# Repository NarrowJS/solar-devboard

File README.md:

## Solar Devboard
An ESP32 C6 mini based devboard that combines zigbee/wifi with solar and lipo charging to easily deploy remote sensing IOT devices.

## Features
- 3.7v Lipo charging circuit and JST connector
- Support for 3v - 18v solar panels
- Reverse polarity protection on solar panel connector
- ADC for lipo charge monitoring
- Power path for charging while on usb-c power
- Extremely compact form factor
- M2 mounting holes

## Why
- Solar panels are extremely useful for remote sensing applications to provide a power source without long wires or very large batteries
- Most solar projects require boost converters and extra breakout boards to connect lipo batteries safely
- Most solar charging boards are too large to be used in compact applications

## BOM
| Reference             | Value                       | Datasheet                                                                         | Footprint                                                  | Qty | DNP | Link                                                                                                                                                                                                                |
|-----------------------|-----------------------------|-----------------------------------------------------------------------------------|------------------------------------------------------------|-----|-----|---------------------------------------------------------------------------------------------------------------------------------------------------------------------------------------------------------------------|
| C1,C2,C4,C5,C10       | 100nF                       | ~                                                                                 | Capacitor_SMD:C_0402_1005Metric                            | 5   |     | https://www.lcsc.com/product-detail/C60474.html?s_z=n_q_100nF%25200402&spm=wm.ssy.bg.0.xh&lcsc_vid=RgcMVwVXQVAIVFxUQVdZVlNSTgBWA1RfFlNeVwIDFAcxVlNRQFRXXl1RT1heUTsOAxUeFF5JWBYZEEoKFBINSQcJGk4%3D                   |
| C3,C6,C12             | 10uF                        | ~                                                                                 | Capacitor_SMD:C_0603_1608Metric                            | 3   |     | https://www.lcsc.com/product-detail/C19702.html?s_z=n_q_10uF%25200603&spm=wm.ssy.bg.0.xh&lcsc_vid=RgcMVwVXQVAIVFxUQVdZVlNSTgBWA1RfFlNeVwIDFAcxVlNRQFdeV1RXRVhcVjsOAxUeFF5JWBYZEEoKFBINSQcJGk4dAgUUFAk%3D            |
| C7                    | 1uF                         | ~                                                                                 | Capacitor_SMD:C_0402_1005Metric                            | 1   |     | https://www.lcsc.com/product-detail/C19702.html?s_z=n_q_10uF%25200603&spm=wm.ssy.bg.0.xh&lcsc_vid=RgcMVwVXQVAIVFxUQVdZVlNSTgBWA1RfFlNeVwIDFAcxVlNRQFdeV1RXRVhcVjsOAxUeFF5JWBYZEEoKFBINSQcJGk4dAgUUFAk%3D            |
| D1                    | CHARGE LED                  | ~                                                                                 | LED_SMD:LED_0805_2012Metric                                | 1   |     | https://www.lcsc.com/product-detail/C19702.html?s_z=n_q_10uF%25200603&spm=wm.ssy.bg.0.xh&lcsc_vid=RgcMVwVXQVAIVFxUQVdZVlNSTgBWA1RfFlNeVwIDFAcxVlNRQFdeV1RXRVhcVjsOAxUeFF5JWBYZEEoKFBINSQcJGk4dAgUUFAk%3D            |
| D2,D3,D4              | 1N5819WS                    | https://datasheet.lcsc.com/lcsc/2204281430_Guangdong-Hottech-1N5819WS_C191023.pdf | Diode_SMD:D_SOD-323                                        | 3   |     | https://www.lcsc.com/product-detail/C191023.html?s_z=n_q_1N5819WS&spm=wm.ssy.bg.0.xh&lcsc_vid=RgcMVwVXQVAIVFxUQVdZVlNSTgBWA1RfFlNeVwIDFAcxVlNRQFdeV1RRQFleUzsOAxUeFF5JWBYZEEoKFBINSQcJGk4dAgUUFAk%3D                |
| IC1                   | RT9080-33GJ5                |                                                                                   | RT9080-33GJ5:SOT94P280X100-5N                              | 1   |     | https://www.lcsc.com/product-detail/C191023.html?s_z=n_q_1N5819WS&spm=wm.ssy.bg.0.xh&lcsc_vid=RgcMVwVXQVAIVFxUQVdZVlNSTgBWA1RfFlNeVwIDFAcxVlNRQFdeV1RRQFleUzsOAxUeFF5JWBYZEEoKFBINSQcJGk4dAgUUFAk%3D                |
| J1                    | USB_C_Receptacle_USB2.0_14P | https://www.usb.org/sites/default/files/documents/usb_type-c.zip                  | Connector_USB:USB_C_Receptacle_HRO_TYPE-C-31-M-12          | 1   |     | https://www.lcsc.com/product-detail/C165948.html?s_z=n_q_type%2520c&spm=wm.ssy.bg.2.xh&lcsc_vid=RgcMVwVXQVAIVFxUQVdZVlNSTgBWA1RfFlNeVwIDFAcxVlNRQFdeV1VQTlhdVzsOAxUeFF5JWBYZEEoKFBINSQcJGk4dAgUUFAk%3D              |
| J2                    | SOLAR_IN +                  | ~                                                                                 | Connector_Wire:SolderWirePad_1x01_SMD_1x2mm                | 1   |     |                                                                                                                                                                                                                     |
| J3                    | SOLAR_IN -                  | ~                                                                                 | Connector_Wire:SolderWirePad_1x01_SMD_1x2mm                | 1   |     |                                                                                                                                                                                                                     |
| J4,J5                 | Conn_01x10_Pin              | ~                                                                                 | Connector_PinHeader_2.54mm:PinHeader_1x10_P2.54mm_Vertical | 2   |     | https://www.lcsc.com/product-detail/C42431810.html?s_z=n_q_pinheader%25201x10&spm=wm.ssy.bg.7.xh&lcsc_vid=RgcMVwVXQVAIVFxUQVdZVlNSTgBWA1RfFlNeVwIDFAcxVlNRQFdeV1BeQFJXXzsOAxUeFF5JWBYZEEoKFBINSQcJGk4dAgUUFAk%3D    |
| J6                    | 4328                        |                                                                                   | 4328:ADAFRUIT_4328                                         | 1   |     | https://www.adafruit.com/product/4328                                                                                                                                                                               |
| P1                    | S2B-PH-SM4-TB               |                                                                                   | S2B-PH-SM4-TB:JST_S2B-PH-SM4-TB                            | 1   |     | https://www.lcsc.com/product-detail/C295747.html?s_z=n_q_S2B-PH-SM4-TB&spm=wm.ssy.bg.1.xh&lcsc_vid=RgcMVwVXQVAIVFxUQVdZVlNSTgBWA1RfFlNeVwIDFAcxVlNRQFdeV1ZVQ1NcVzsOAxUeFF5JWBYZEEoKFBINSQcJGk4dAgUUFAk%3D           |
| Q2                    | AO3401A                     | http://www.aosmd.com/pdfs/datasheet/AO3401A.pdf                                   | Package_TO_SOT_SMD:SOT-23                                  | 1   |     | https://www.lcsc.com/product-detail/C15127.html?s_z=n_q_AO3401A&spm=wm.ssy.bg.0.xh&lcsc_vid=RgcMVwVXQVAIVFxUQVdZVlNSTgBWA1RfFlNeVwIDFAcxVlNRQFdeV1ZTRlRcUDsOAxUeFF5JWBYZEEoKFBINSQcJGk4dAgUUFAk%3D                  |
| R1,R2                 | 5k1                         | ~                                                                                 | Resistor_SMD:R_0603_1608Metric                             | 2   |     | https://www.lcsc.com/product-detail/C15127.html?s_z=n_q_AO3401A&spm=wm.ssy.bg.0.xh&lcsc_vid=RgcMVwVXQVAIVFxUQVdZVlNSTgBWA1RfFlNeVwIDFAcxVlNRQFdeV1ZTRlRcUDsOAxUeFF5JWBYZEEoKFBINSQcJGk4dAgUUFAk%3D                  |
| R3,R4,R5,R6,R8,R9,R10 | 10k                         | ~                                                                                 | Resistor_SMD:R_0603_1608Metric                             | 7   |     | https://www.lcsc.com/product-detail/C98220.html?s_z=n_q_10k%25200603&spm=wm.ssy.bg.0.xh&lcsc_vid=RgcMVwVXQVAIVFxUQVdZVlNSTgBWA1RfFlNeVwIDFAcxVlNRQFdeV1dUQVVeVjsOAxUeFF5JWBYZEEoKFBINSQcJGk4dAgUUFAk%3D             |
| R7                    | 1k                          | ~                                                                                 | Resistor_SMD:R_0603_1608Metric                             | 1   |     | https://www.lcsc.com/product-detail/C2907002.html?s_z=n_q_1k%25200603&spm=wm.ssy.bg.1.xh&lcsc_vid=RgcMVwVXQVAIVFxUQVdZVlNSTgBWA1RfFlNeVwIDFAcxVlNRQFdeV1dVTllXVDsOAxUeFF5JWBYZEEoKFBINSQcJGk4dAgUUFAk%3D            |
| R11                   | 27k                         | ~                                                                                 | Resistor_SMD:R_0603_1608Metric                             | 1   |     | https://www.lcsc.com/product-detail/C22967.html?s_z=n_q_27k%25200603&spm=wm.ssy.bg.0.xh&lcsc_vid=RgcMVwVXQVAIVFxUQVdZVlNSTgBWA1RfFlNeVwIDFAcxVlNRQFdeV1dQRFNXUTsOAxUeFF5JWBYZEEoKFBINSQcJGk4dAgUUFAk%3D             |
| R12,R15               | 100k                        | ~                                                                                 | Resistor_SMD:R_0603_1608Metric                             | 2   |     | https://www.lcsc.com/product-detail/C14675.html?s_z=n_q_100k%25200603&spm=wm.ssy.bg.0.xh&lcsc_vid=RgcMVwVXQVAIVFxUQVdZVlNSTgBWA1RfFlNeVwIDFAcxVlNRQFdeV1BWQVdeUTsOAxUeFF5JWBYZEEoKFBINSQcJGk4dAgUUFAk%3D            |
| SW1,SW2               | PTS810_SJM_250_SMTR_LFS     |                                                                                   | PTS810_SJM_250_SMTR_LFS:SW_PTS810_SJM_250_SMTR_LFS         | 2   |     | https://www.lcsc.com/product-detail/C116501.html?s_z=n_q_PTS810_SJM_250_SMTR_LFS&spm=wm.ssy.bg.0.xh&lcsc_vid=RgcMVwVXQVAIVFxUQVdZVlNSTgBWA1RfFlNeVwIDFAcxVlNRQFdeV1dfR1ldUDsOAxUeFF5JWBYZEEoKFBINSQcJGk4dAgUUFAk%3D |
| U1                    | ESP32-C6-MINI-1-H4          |                                                                                   | ESP32-C6-MINI-1-H4:XCVR_ESP32-C6-MINI-1-H4                 | 1   |     | https://www.lcsc.com/product-detail/C5736265.html?s_z=n_q_esp32&spm=wm.ssy.bg.25.xh&lcsc_vid=RgcMVwVXQVAIVFxUQVdZVlNSTgBWA1RfFlNeVwIDFAcxVlNRQFdeV1BUQFhZUzsOAxUeFF5JWBYZEEoKFBINSQcJGk4dAgUUFAk%3D                 |
| U2                    | PQ25186DLHR                 | https://www.ti.com/lit/gpn/bq25186                                                | BQ25186:WSON10_DLH_TEX                                     | 1   |     | https://www.lcsc.com/product-detail/C44639442.html?s_z=n_q_PQ25186DLHR&spm=wm.ssy.bg.0.xh&lcsc_vid=RgcMVwVXQVAIVFxUQVdZVlNSTgBWA1RfFlNeVwIDFAcxVlNRQFdeV1BQRFdZVDsOAxUeFF5JWBYZEEoKFBINSQcJGk4dAgUUFAk%3D           |

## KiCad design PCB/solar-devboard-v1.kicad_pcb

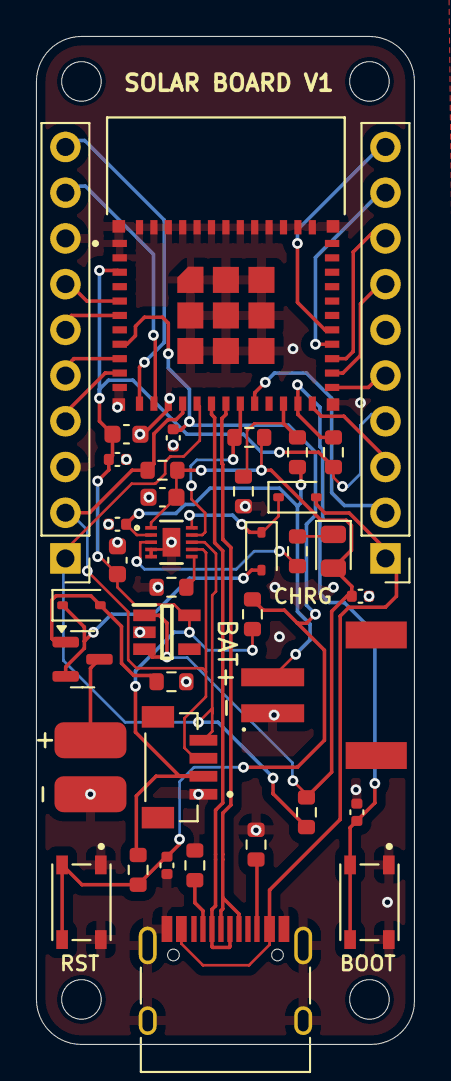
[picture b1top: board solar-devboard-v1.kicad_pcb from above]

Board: 2 copper layers, 21.0 x 56.0 mm, 43 parts (0 on the bottom side), 35 nets.

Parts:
3-18V: SOLAR_IN +; SolderWirePad_1x01_SMD_1x2mm
BOOT: PTS810_SJM_250_SMTR_LFS; SW_PTS810_SJM_250_SMTR_LFS
C1, C2, C4, C5, C10: 100nF; C_0402_1005Metric
C3, C6, C12: 10uF; C_0603_1608Metric
C7: 1uF; C_0402_1005Metric
D1: CHARGE LED; LED_0805_2012Metric
D2, D3, D4: 1N5819WS; D_SOD-323
H1, H2, H3, H4: MountingHole; MountingHole_2.2mm_M2
IC1: RT9080-33GJ5; SOT94P280X100-5N
J1: USB_C_Receptacle_USB2.0_14P; USB_C_Receptacle_HRO_TYPE-C-31-M-12
J4, J5: Conn_01x10_Pin; PinHeader_1x10_P2.54mm_Vertical
J6: 4328; ADAFRUIT_4328
P1: S2B-PH-SM4-TB; JST_S2B-PH-SM4-TB
Q2: AO3401A; SOT-23
R1, R2: 5k1; R_0603_1608Metric
R3, R4, R5, R6, R8, R9, R10: 10k; R_0603_1608Metric
R7: 1k; R_0603_1608Metric
R11: 27k; R_0603_1608Metric
R12, R15: 100k; R_0603_1608Metric
RST: PTS810_SJM_250_SMTR_LFS; SW_PTS810_SJM_250_SMTR_LFS
U1: ESP32-C6-MINI-1-H4; XCVR_ESP32-C6-MINI-1-H4
U2: PQ25186DLHR; WSON10_DLH_TEX
_: SOLAR_IN -; SolderWirePad_1x01_SMD_1x2mm

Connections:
+3.3V: C2.1, C3.1, C12.1, IC1.5 (VOUT), J5.4, J6.2, R3.1, R4.1, R5.1, U1.3 (3V3)
+BAT: C7.1, P1.2, R11.2, U2.2 (BAT)
+SOLAR: D3.1 (K), D4.2 (A), Q2.2 (S)
+SYS: C6.1, C10.1, D1.2 (A), IC1.1 (VIN), IC1.3 (EN), R8.2, R9.2, R10.2, U2.1 (SYS)
BAT_LVL: R11.1, R12.2, U1.22 (IO8)
CHIP_PU: C1.1, C5.1, R3.2, R5.2, RST.3, RST.4, U1.8 (EN)
GND: BOOT.1, BOOT.2, C1.2, C2.2, C3.2, C4.2, C5.2, C6.2, C7.2, C10.2, C12.2, IC1.2 (GND), J1.A1 (GND), J1.A12 (GND), J1.B1 (GND), J1.B12 (GND), J1.S1 (SHIELD), J4.3, J4.8, J5.6, J6.1, P1.1, R1.2, R2.2, R6.2, R12.1, R15.1, RST.1, RST.2, U1.1 (GND1), U1.2 (GND1), U1.11 (GND1), U1.14 (GND1), U1.36 (GND1), U1.37 (GND1), U1.38 (GND1), U1.39 (GND1), U1.40 (GND1), U1.41 (GND1), U1.42 (GND1), U1.43 (GND1), U1.44 (GND1), U1.45 (GND1), U1.46 (GND1), U1.47 (GND2), U1.48 (GND2), U1.49_1 (GND2), U1.49_2 (GND2), U1.49_3 (GND2), U1.49_4 (GND2), U1.49_5 (GND2), U1.49_6 (GND2), U1.49_7 (GND2), U1.49_8 (GND2), U1.49_9 (GND2), U1.50 (GND2), U1.51 (GND2), U1.52 (GND2), U1.53 (GND2), U2.4 (/CE), U2.5 (GND), U2.11 (EPAD), _.1
GPIO0: J4.10, U1.12 (IO0)
GPIO1: J4.9, U1.13 (IO1)
GPIO2: J4.7, U1.5 (IO2)
GPIO3: J4.6, U1.6 (IO3)
GPIO4: J4.5, U1.9 (IO4)
GPIO5: J4.4, U1.10 (IO5)
GPIO9: BOOT.3, BOOT.4, C4.1, R4.2, U1.23 (IO9)
GPIO14: R8.1, U1.19 (IO14), U2.9 (/INT)
GPIO15: J5.2, U1.20 (IO15)
GPIO18: J5.3, U1.24 (IO18)
GPIO19: J5.5, U1.25 (IO19)
GPIO20: J5.7, U1.26 (IO20)
GPIO21: J5.8, U1.27 (IO21)
GPIO22: J5.9, U1.28 (IO22)
GPIO23: J5.10, U1.29 (IO23)
IN+: D2.1 (K), D4.1 (K), U2.10 (IN)
unnamed: D1.1 (K), R7.1
unnamed: D3.2 (A), Q2.1 (G), R15.2
unnamed: J1.A5 (CC1), R2.1
unnamed: J1.B5 (CC2), R1.1
unnamed: 3-18V.1, Q2.3 (D)
unnamed: R6.1, U2.6 (TS/MR)
unnamed: R7.2, U2.3 (/PG/GPO)
SCL: J4.1, J6.4, R10.1, U1.16 (IO7), U2.8 (SCL)
SDA: J4.2, J6.3, R9.1, U1.15 (IO6), U2.7 (SDA)
USB_D+: J1.A6 (D+), J1.B6 (D+), U1.18 (IO13)
USB_D-: J1.A7 (D-), J1.B7 (D-), U1.17 (IO12)
VBUS: D2.2 (A), J1.A4 (VBUS), J1.A9 (VBUS), J1.B4 (VBUS), J1.B9 (VBUS), J5.1

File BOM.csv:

Reference,Value,Datasheet,Footprint,Qty,DNP,Link
"C1,C2,C4,C5,C10",100nF,~,Capacitor_SMD:C_0402_1005Metric,5,,https://www.lcsc.com/product-detail/C60474.html?s_z=n_q_100n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
"C3,C6,C12",10uF,~,Capacitor_SMD:C_0603_1608Metric,3,,https://www.lcsc.com/product-detail/C19702.html?s_z=n_q_10uF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
C7,1uF,~,Capacitor_SMD:C_0402_1005Metric,1,,https://www.lcsc.com/product-detail/C19702.html?s_z=n_q_10uF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
D1,CHARGE LED,~,LED_SMD:LED_0805_2012Metric,1,,https://www.lcsc.com/product-detail/C19702.html?s_z=n_q_10uF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
"D2,D3,D4",1N5819WS,https://datasheet.lcsc.com/lcsc/2204281430_Guangdong-Hottech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,Diode_SMD:D_SOD-323,3,,https://www.lcsc.com/product-detail/C191023.html?s_z=n_q_1N5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
IC1,RT9080-33GJ5,,RT9080-33GJ5:SOT94P280X100-5N,1,,https://www.lcsc.com/product-detail/C191023.html?s_z=n_q_1N5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
J1,USB_C_Receptacle_USB2.0_14P,https://www.usb.org/sites/default/files/documents/usb_type-c.zip,Connector_USB:USB_C_Receptacle_HRO_TYPE-C-31-M-12,1,,https://www.lcsc.com/product-detail/C165948.html?s_z=n_q_typ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
J2,SOLAR_IN +,~,Connector_Wire:SolderWirePad_1x01_SMD_1x2mm,1,,
J3,SOLAR_IN -,~,Connector_Wire:SolderWirePad_1x01_SMD_1x2mm,1,,
"J4,J5",Conn_01x10_Pin,~,Connector_PinHeader_2.54mm:PinHeader_1x10_P2.54mm_Vertical,2,,https://www.lcsc.com/product-detail/C42431810.html?s_z=n_q_p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
J6,4328,,4328:ADAFRUIT_4328,1,,https://www.adafruit.com/product/4328
P1,S2B-PH-SM4-TB,,S2B-PH-SM4-TB:JST_S2B-PH-SM4-TB,1,,https://www.lcsc.com/product-detail/C295747.html?s_z=n_q_S2B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
Q2,AO3401A,http://www.aosmd.com/pdfs/datasheet/AO3401A.pdf,Package_TO_SOT_SMD:SOT-23,1,,https://www.lcsc.com/product-detail/C15127.html?s_z=n_q_AO34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
"R1,R2",5k1,~,Resistor_SMD:R_0603_1608Metric,2,,https://www.lcsc.com/product-detail/C15127.html?s_z=n_q_AO34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
"R3,R4,R5,R6,R8,R9,R10",10k,~,Resistor_SMD:R_0603_1608Metric,7,,https://www.lcsc.com/product-detail/C98220.html?s_z=n_q_10k%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
R7,1k,~,Resistor_SMD:R_0603_1608Metric,1,,https://www.lcsc.com/product-detail/C2907002.html?s_z=n_q_1k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
R11,27k,~,Resistor_SMD:R_0603_1608Metric,1,,https://www.lcsc.com/product-detail/C22967.html?s_z=n_q_27k%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
"R12,R15",100k,~,Resistor_SMD:R_0603_1608Metric,2,,https://www.lcsc.com/product-detail/C14675.html?s_z=n_q_100k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
"SW1,SW2",PTS810_SJM_250_SMTR_LFS,,PTS810_SJM_250_SMTR_LFS:SW_PTS810_SJM_250_SMTR_LFS,2,,https://www.lcsc.com/product-detail/C116501.html?s_z=n_q_PTS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
U1,ESP32-C6-MINI-1-H4,,ESP32-C6-MINI-1-H4:XCVR_ESP32-C6-MINI-1-H4,1,,https://www.lcsc.com/product-detail/C5736265.html?s_z=n_q_es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
U2,PQ25186DLHR,https://www.ti.com/lit/gpn/bq25186,BQ25186:WSON10_DLH_TEX,1,,https://www.lcsc.com/product-detail/C44639442.html?s_z=n_q_P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

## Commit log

2026-05-01 Initialize README with project details and features
    Added detailed project description, features, and BOM link.
2026-05-01 Update README with detailed BOM and features
2026-05-01 Update README with reverse polarity protection feature
    Added reverse polarity protection to the solar panel connector in the features section.
2026-05-01 'firmware'
2026-05-01 update bom price
2026-05-01 added temperature code in ino
